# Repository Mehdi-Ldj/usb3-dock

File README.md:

# USB-C Dock with Gigabit Ethernet — Rev A

A 130 × 85 mm, four-layer dock built around a 7-port USB 3.2 Gen 1 hub:
Gigabit Ethernet, three USB-A ports, a USB-C downstream port and a USB 2.0
port, with every external port measured and protected.

## Design viewer

| Schematic | Board |
|:---:|:---:|
| [Schematic, seven pages (PDF)](docs/renders/schematic-rev-a.pdf) | [Open the PCB in KiCanvas][kicanvas] |

The PCB opens in the browser viewer; the schematic is hierarchical — a root
sheet and six children — which KiCanvas does not traverse, so it is published
as one PDF instead.

[kicanvas]: https://kicanvas.org/?repo=https%3A%2F%2Fgithub.com%2FMehdi-Ldj%2Fusb3-dock%2Fblob%2Fmain%2Fhardware%2Frev-a%2Fusb3-dock.kicad_pcb

## Overview

Power and data arrive on **two separate USB-C ports**. `J1` is a USB-C PD input
that negotiates 12 V and feeds the converters; `J2` is the upstream port that
presents the dock to the host as USB 3.2 Gen 1 — SuperSpeed plus USB 2.0.

Three choices shaped the board more than anything else:

- **The channel is budgeted, not assumed.** Every SuperSpeed pair runs in a
  90 Ω class on the outer layers over a solid inner ground, and the whole path
  from hub pin to connector was cascaded against a 6.5 dB budget before layout.
- **Every port is measured.** Five INA219 sit on 0.1 Ω shunts, one per external
  port, sharing one bus with no mux, so a fault is a number rather than a guess.
- **Power is poured, not routed.** Both inner layers are ground so that *both*
  outer layers can carry controlled-impedance pairs; the 5 V rail is a pour on
  the bottom layer instead of a trunk of tracks.

## Features

- **7-port USB 3.2 Gen 1** hub (USB5807C), 5 Gbps per port
- **Gigabit Ethernet** via LAN7800 with an integrated PHY and an RJ45 magjack
- **USB-C PD input** (CH224A) negotiating 12 V
- 12 V → **5 V @ 6 A**, 3.3 V and 1.2 V local rails
- **Per-port measurement** — five INA219 on 0.1 Ω shunts, one bus, no mux
- **Per-port protection** — under 100 ms trip, latched, retried at 2 s / 10 s / 60 s
- SuperSpeed muxing to the USB-C port (HD3SS3212, 2:1)
- **130 × 85 mm, 4-layer**, controlled impedance on 26 differential pairs
- Thermal and ESD design for a self-powered dock: 5 V pour on B.Cu, TVS on the input

## Board specifications

| Item | Value |
|---|---|
| Board size | **130 × 85 mm**, 4 layers |
| Stackup | **JLC04161H-3313**, FR4, 1.6 mm nominal |
| Copper | 1 oz outer, 0.5 oz inner, ENIG finish, green mask, white silk |
| Reference planes | **L2 and L3, both solid ground**, unbroken under every pair |
| Minimum feature | 0.15 mm track, 0.11 mm clearance, 0.20 mm drill |
| Vias | 0.20/0.50 mm and 0.30/0.60 mm, tented, no blind or buried |
| Impedance | 90 Ω SS/HS, 100 Ω MDI, 50 Ω single-ended, all ±10 % |
| Assembly | JLCPCB Standard PCBA |

## Architecture

Line colour and weight separate the five signal classes: power, SuperSpeed,
USB 2.0, Ethernet MDI and control. The PD sink on `J1` produces the 12 V rail,
which is fused and clamped before the 5 V converter; the hub fans out to the
three USB-A ports, the USB-C port through the mux, the Ethernet bridge and the
USB 2.0 port. Port power and sensing sit below the hub, between the 5 V rail and
the five VBUS outputs: the switches gate each port, the shunts measure it, and
the console sets enables and reads the measurements over the control lines.

## Design notes

### SuperSpeed channel

Every SuperSpeed and USB 2.0 pair runs at 0.180/0.150 mm in its 90 Ω class on
L1 or L4, over a solid inner ground. The outer dielectric is 3313 prepreg,
which keeps a 90 Ω pair to 0.51 mm of width and lets the fan-outs fit under the
0.4 mm hub.

The channel is closed by analysis rather than by hope: trace, AC coupling,
vias, launches and the mux S-parameters cascade to **−2.58 dB at 2.5 GHz**
against a **6.5 dB** budget, with the mux contributing 0.85 dB of it. The
100 nF AC-coupling capacitors sit on the transmit side at the connector, where
the ESD diodes already are.

Because a 1.5 mm tuning meander cannot fit inside a 2.0 mm uncoupled window,
the allowance for uncoupled length is 3.0 mm, and the two runs that exceed it
are recorded rather than hidden.

### Power and thermals

The 12 V input is fused at 3 A and clamped by an SMBJ15A before the
TPS56C215 buck, which holds 5 V at 6 A. That converter was chosen on junction
temperature, not on current: 5 V at 6 A in a 3.5 × 3.5 mm QFN sits at roughly
94 °C junction at 40 °C ambient, and the 2 × 3 mm class was rejected on its
measured thermal resistance.

The 5 V rail is a pour on B.Cu rather than a trunk of tracks. That took the
drop at a fully loaded port from 231 mV to 27 mV and cut the copper loss from
about 750 mW to under 100 mW.

### Ethernet

The LAN7800 carries the MDI on a 100 Ω class to a magjack with integrated
magnetics and a Bob Smith termination, so no discrete transformer or common-mode
choke is needed. The MDI pairs are length-matched and stay on L1 for the whole
run.

### Port sensing and protection

Each external port has a TPS2065 switch and a 0.1 Ω shunt with an INA219 across
it, so current, voltage and power are measured rather than inferred. The hub's
port-power and overcurrent sense share one pin per port; the controller joins
that node with an open-drain pin, making it a wired-OR — either side can force a
port off, neither can force one on.

### Package and assembly

Four layers carry the 0.4 mm hub fan-out on the top, both inner layers as solid
ground, and the signal pairs on the bottom. The QFNs and the magjack have pads
underneath, so assembly is a stencil-and-reflow job rather than hand work; the
placement file carries the rotation corrections the assembler's part library
needs, measured once against their preview.

## Layout

| Front copper | Back copper |
|:---:|:---:|
|  |  |
| **Inner 1 — ground plane** | **Inner 2 — ground plane** |
|  |  |

Both inner layers are unbroken ground; the 5 V pour is the large region on the
back copper. The top view of the assembled board is
[`board-3d-top.png`](docs/renders/board-3d-top.png).

## Repository structure

| Path | Contents |
|---|---|
| `hardware/rev-a/` | KiCad 10 project: six schematic sheets, PCB, symbol and footprint libraries, 3D models, JLCPCB BOM |
| `docs/` | [BOM](docs/BOM.md), block diagram, board renders, schematic PDF |
| `LICENSE` | CERN Open Hardware Licence v2 — Permissive |

Open the project with KiCad 10:

```bash
kicad hardware/rev-a/usb3-dock.kicad_pro
```

## Fabrication and assembly

The board is drawn for JLCPCB 4-layer fabrication on the **JLC04161H-3313**
stackup with impedance control enabled at ±10 %, and for Standard PCBA with the
stencil and reflow that the QFN packages require.

The fabrication package for a release — gerbers, drill file, job file, BOM and
CPL — is attached to the release rather than committed here.

## Status

**Rev A is frozen and has not been fabricated yet.** The design is complete
through DRC, ERC and schematic/board parity.

## Licence

Released under the [CERN Open Hardware Licence Version 2 – Permissive](LICENSE).

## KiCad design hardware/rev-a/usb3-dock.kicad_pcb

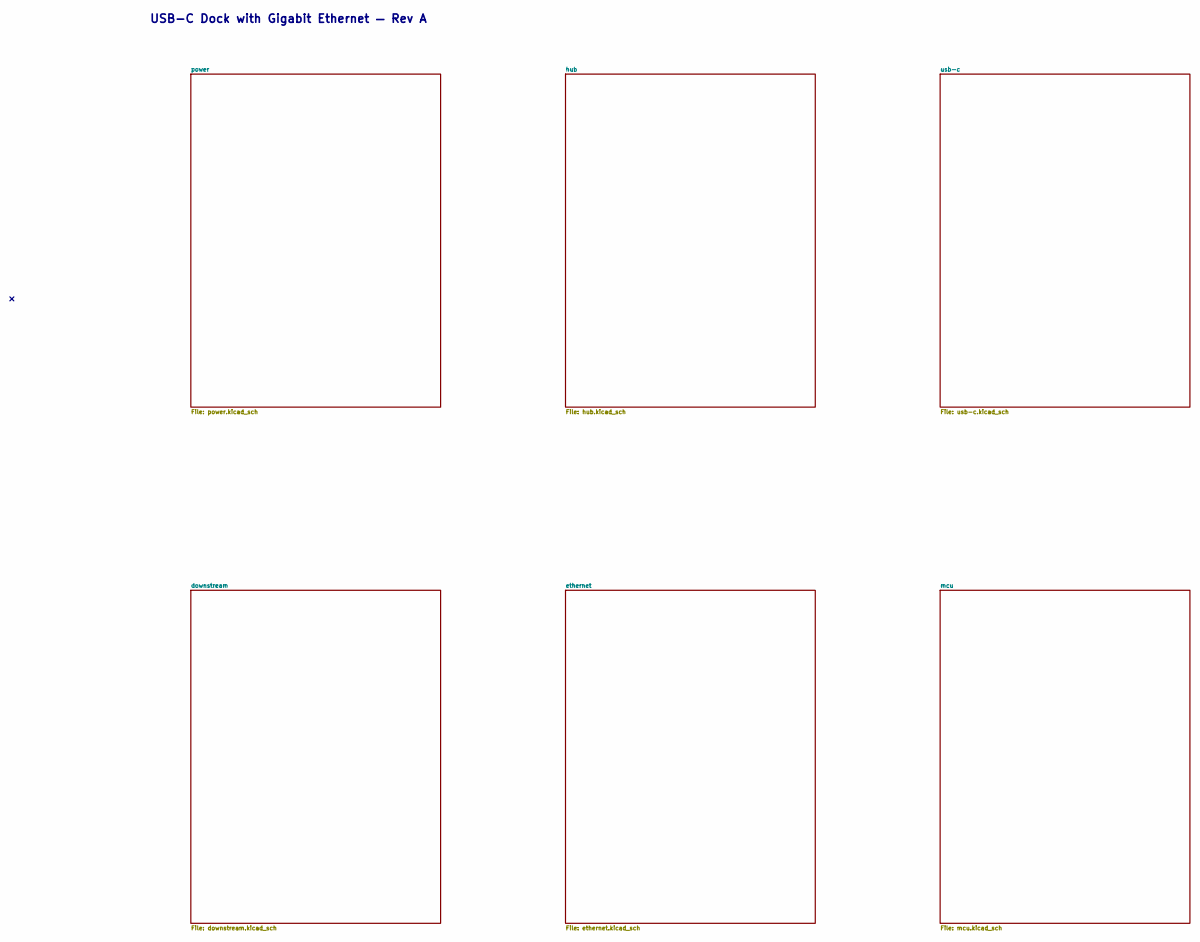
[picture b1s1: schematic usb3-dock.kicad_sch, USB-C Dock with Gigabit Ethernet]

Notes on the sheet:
USB-C Dock with Gigabit Ethernet — Rev A

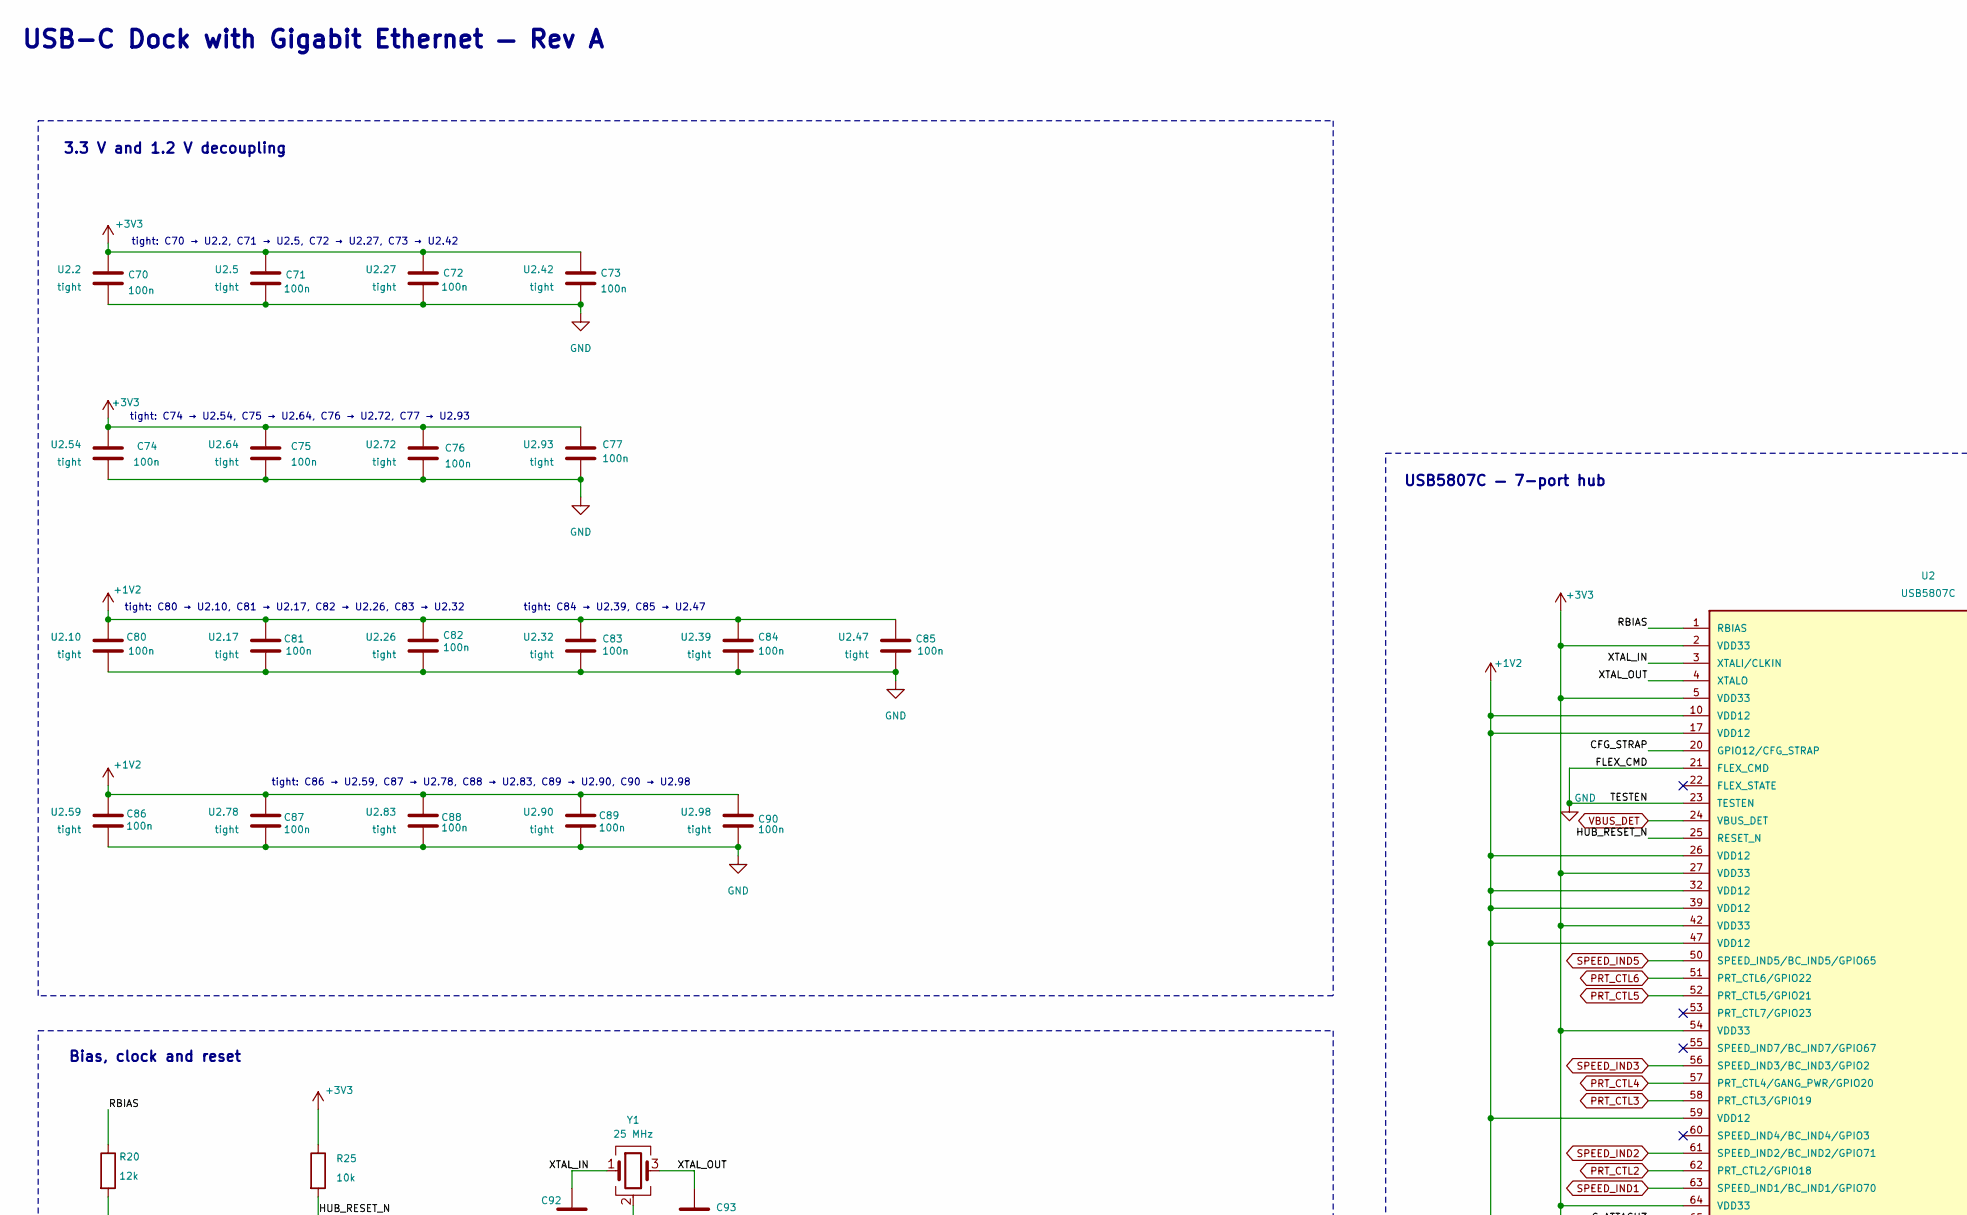
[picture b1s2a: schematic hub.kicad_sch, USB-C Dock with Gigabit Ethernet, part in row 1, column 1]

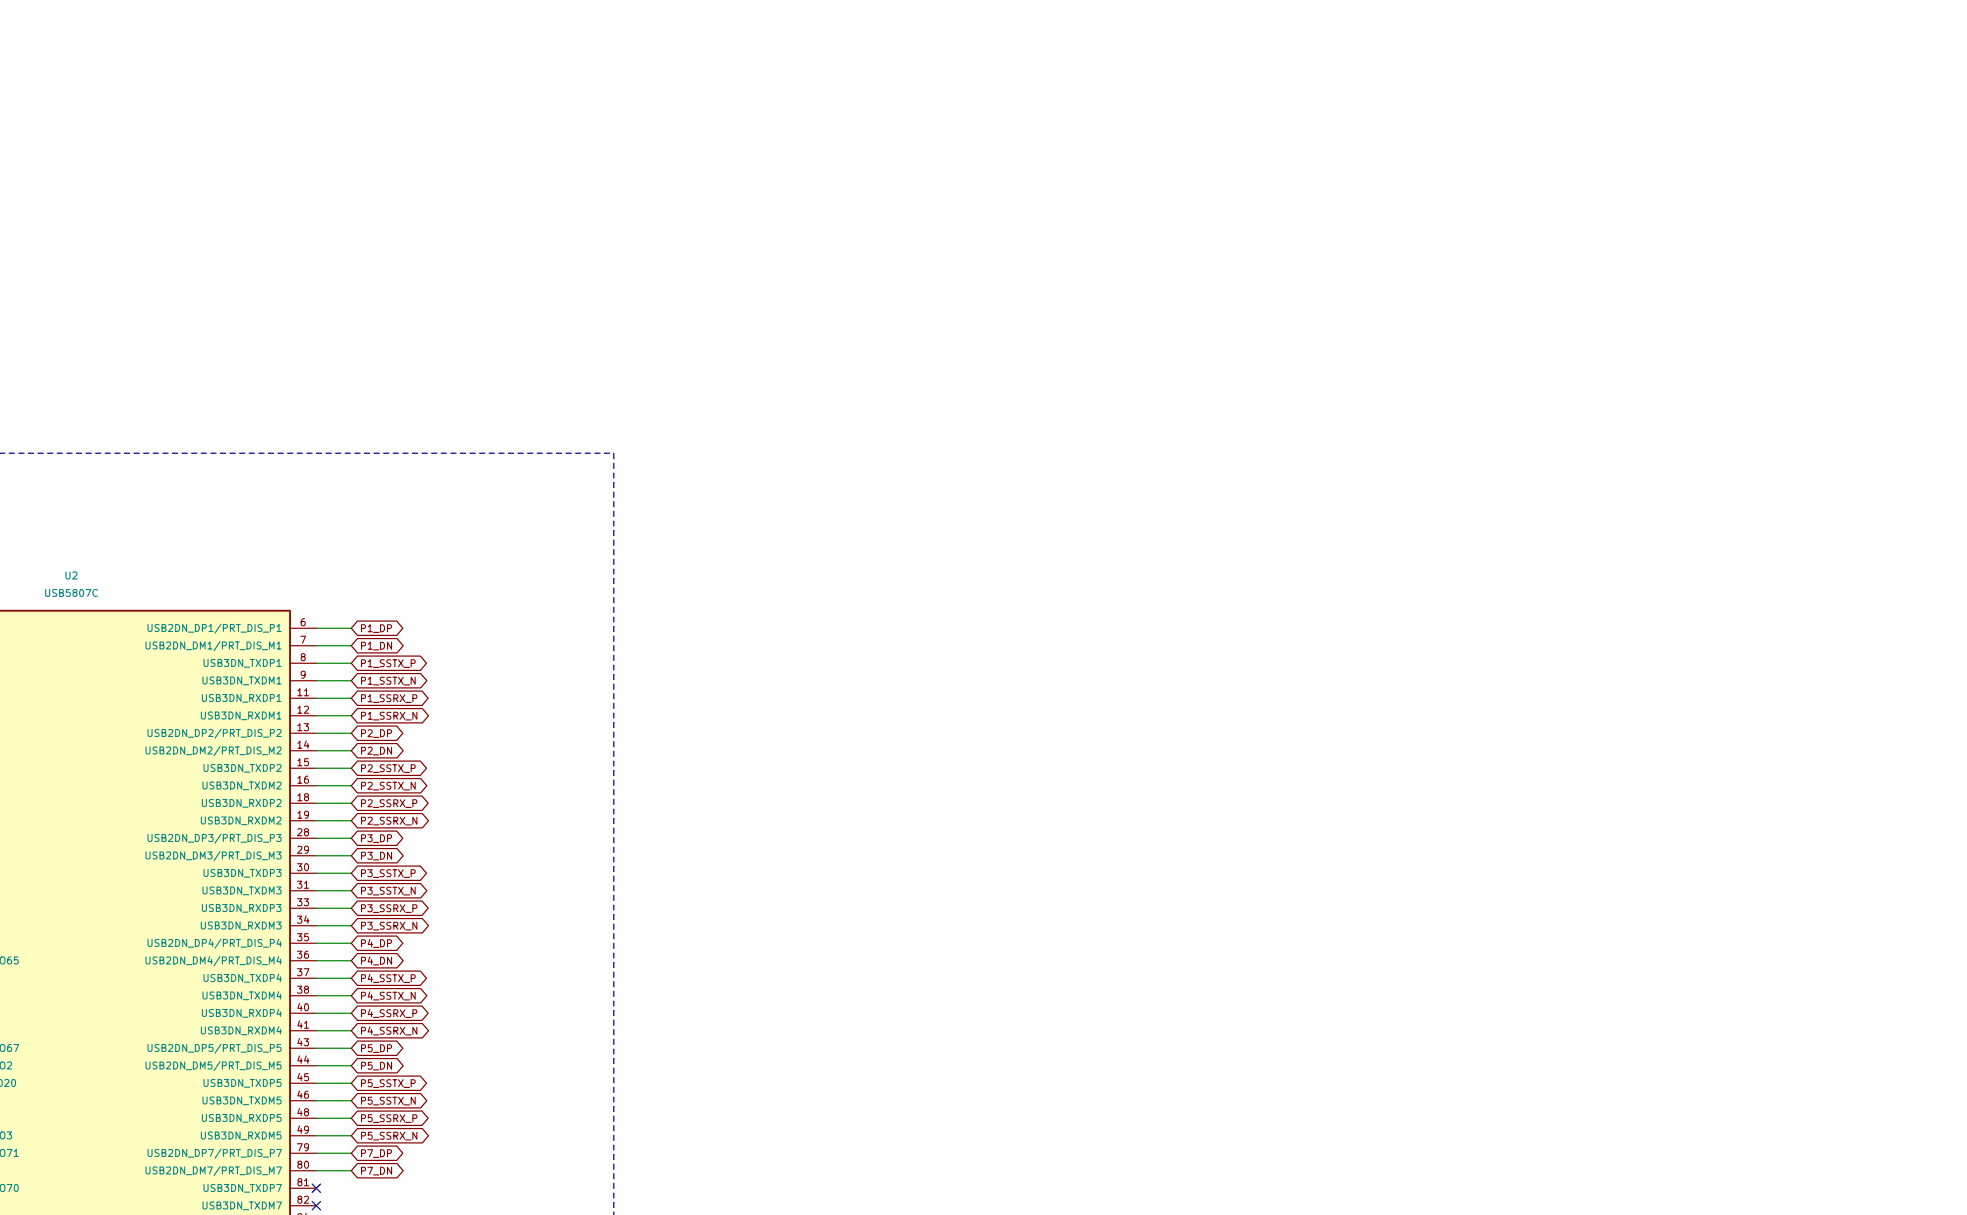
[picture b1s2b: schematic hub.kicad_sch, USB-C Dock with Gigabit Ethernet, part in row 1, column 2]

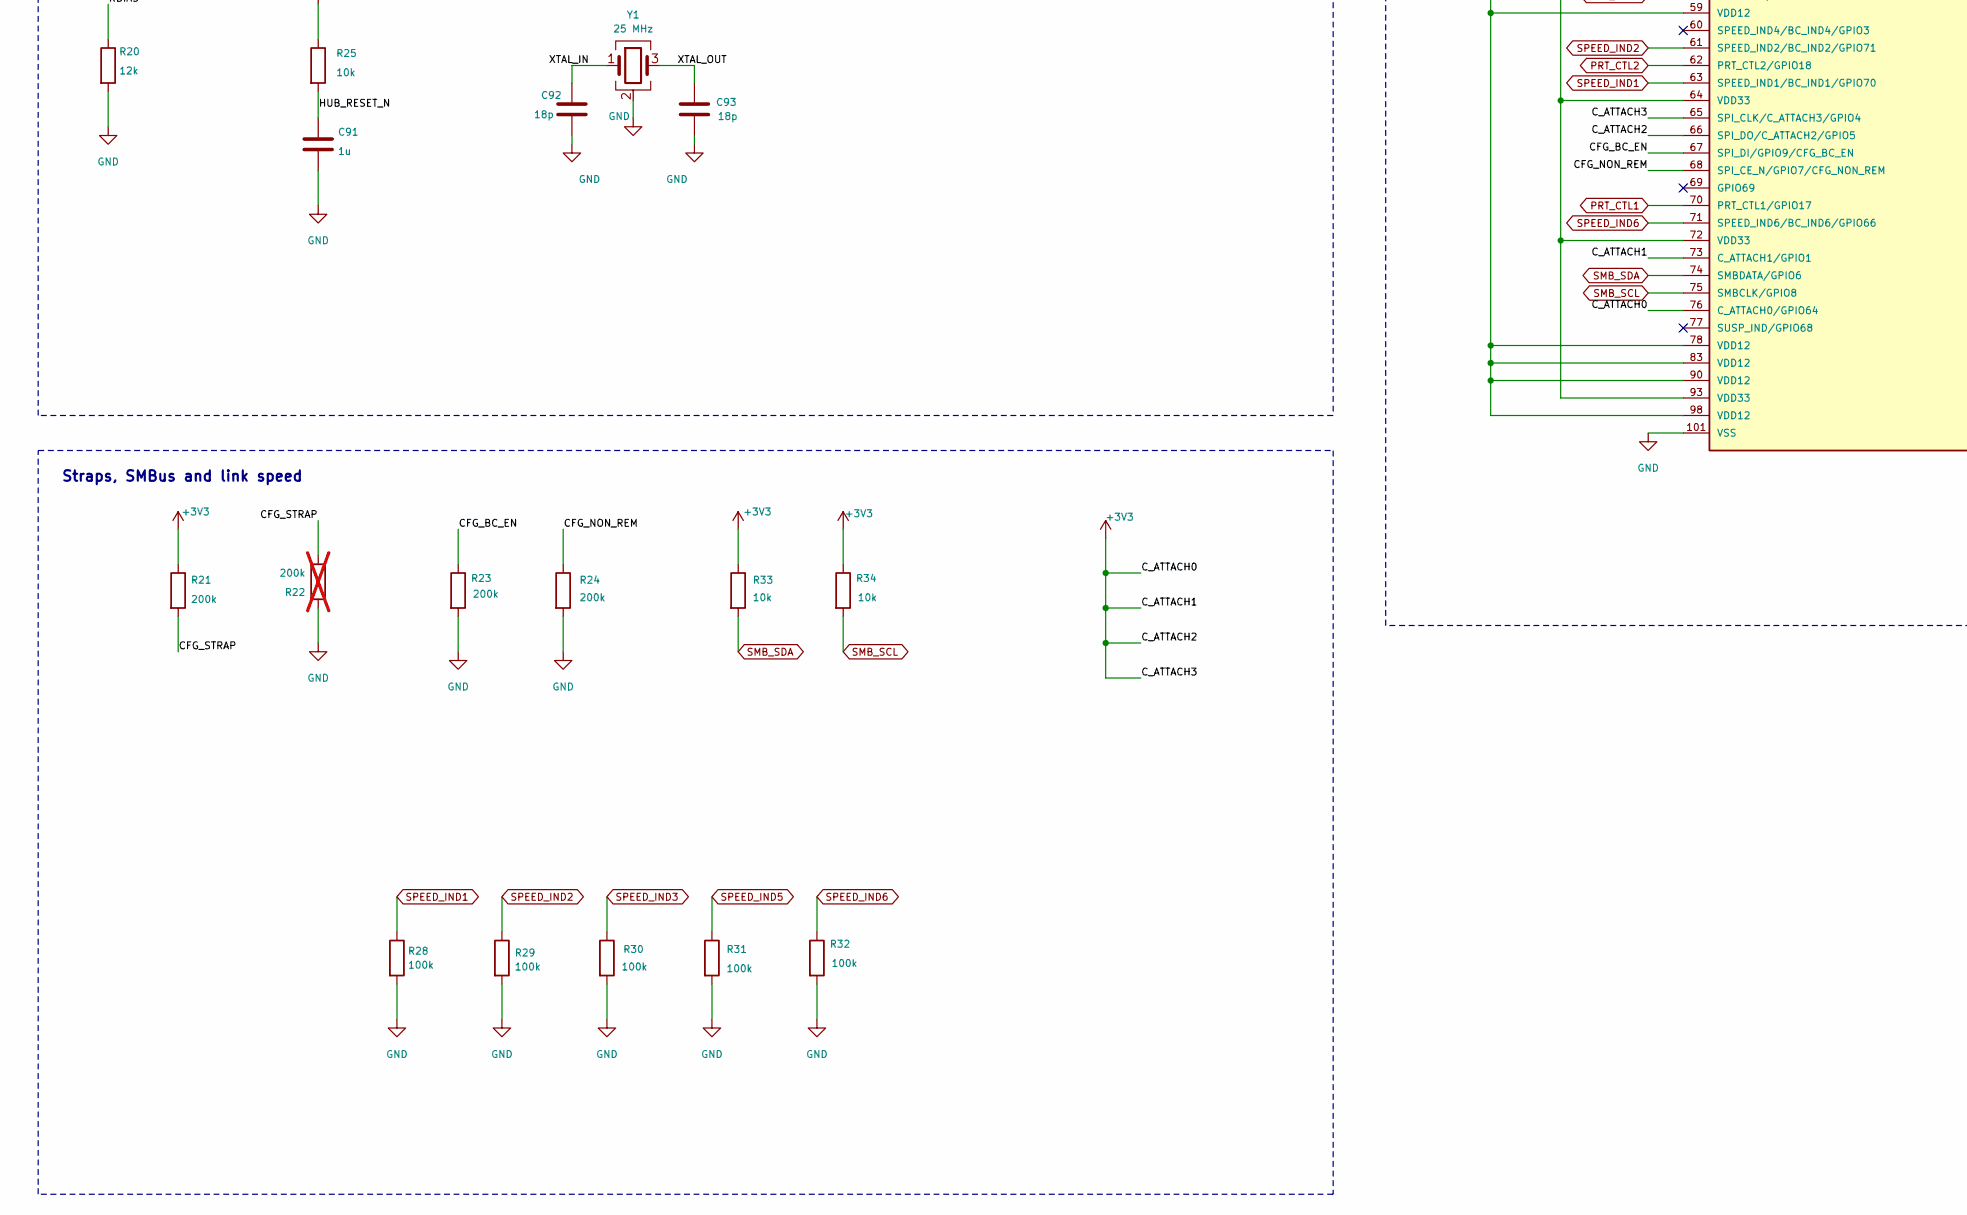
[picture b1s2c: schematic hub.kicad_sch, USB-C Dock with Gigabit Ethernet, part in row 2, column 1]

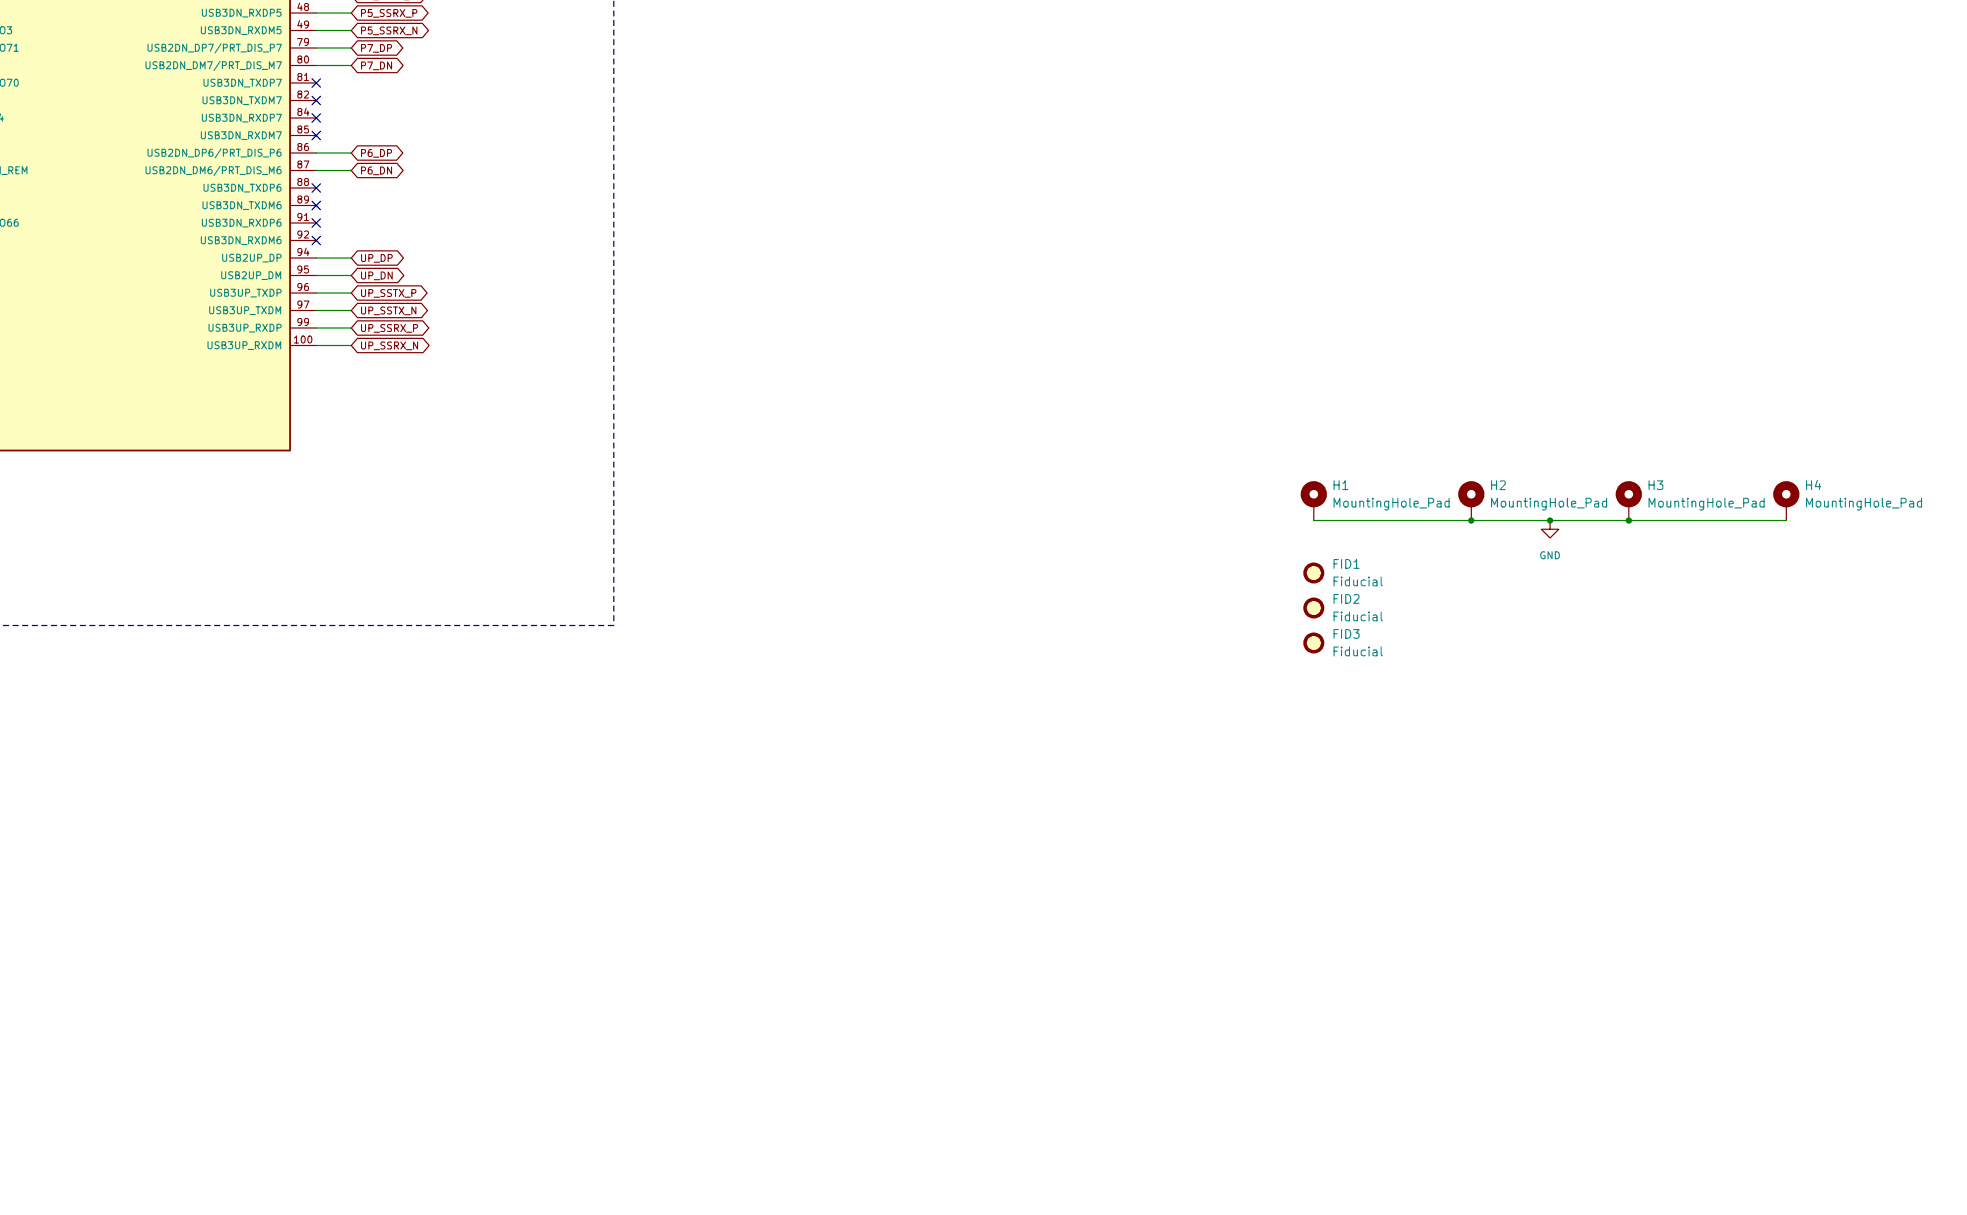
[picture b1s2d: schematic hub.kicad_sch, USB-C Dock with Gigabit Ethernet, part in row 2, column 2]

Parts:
C70, C71, C72, C73, C74, C75, C76, C77, C80, C81, C82, C83, C84, C85, C86, C87, C88, C89, C90: 100n; C_0402_1005Metric
C91: 1u; C_0603_1608Metric
C92, C93: 18p; C_0402_1005Metric
FID1, FID2, FID3: Fiducial; Fiducial_1mm_Mask2mm
H1, H2, H3, H4: MountingHole_Pad; MountingHole_3.5mm_Pad_Via
R20: 12k; R_0603_1608Metric
R21, R23, R24: 200k; R_0603_1608Metric
R22: 200k; R_0603_1608Metric; not fitted
R25, R33, R34: 10k; R_0603_1608Metric
R28, R29, R30, R31, R32: 100k; R_0603_1608Metric
U2: USB5807C; VQFN-100-1EP_12x12mm_P0.4mm_EP8x8mm
Y1: 25 MHz; Crystal_SMD_3225-4Pin_3.2x2.5mm

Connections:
+1V2: C80.1, C81.1, C82.1, C83.1, C84.1, C85.1, C86.1, C87.1, C88.1, C89.1, C90.1, U2.10 (VDD12), U2.17 (VDD12), U2.26 (VDD12), U2.32 (VDD12), U2.39 (VDD12), U2.47 (VDD12), U2.59 (VDD12), U2.78 (VDD12), U2.83 (VDD12), U2.90 (VDD12), U2.98 (VDD12); also elsewhere on the board
+3V3: C70.1, C71.1, C72.1, C73.1, C74.1, C75.1, C76.1, C77.1, R21.1, R25.1, R33.1, R34.1, U2.2 (VDD33), U2.5 (VDD33), U2.27 (VDD33), U2.42 (VDD33), U2.54 (VDD33), U2.64 (VDD33), U2.65 (SPI_CLK/C_ATTACH3/GPIO4), U2.66 (SPI_DO/C_ATTACH2/GPIO5), U2.72 (VDD33), U2.73 (C_ATTACH1/GPIO1), U2.76 (C_ATTACH0/GPIO64), U2.93 (VDD33); also elsewhere on the board
/hub/CFG_BC_EN: R23.1, U2.67 (SPI_DI/GPIO9/CFG_BC_EN)
/hub/CFG_NON_REM: R24.1, U2.68 (SPI_CE_N/GPIO7/CFG_NON_REM)
/hub/CFG_STRAP: R21.2, R22.2, U2.20 (GPIO12/CFG_STRAP)
/hub/HUB_RESET_N: C91.1, R25.2, U2.25 (RESET_N)
/hub/RBIAS: R20.1, U2.1 (RBIAS)
/hub/XTAL_IN: C92.1, U2.3 (XTALI/CLKIN), Y1.1
/hub/XTAL_OUT: C93.1, U2.4 (XTALO), Y1.3
GND: C70.2, C71.2, C72.2, C73.2, C74.2, C75.2, C76.2, C77.2, C80.2, C81.2, C82.2, C83.2, C84.2, C85.2, C86.2, C87.2, C88.2, C89.2, C90.2, C91.2, C92.2, C93.2, H1.1 (1_1), H2.1 (1_1), H3.1 (1_1), H4.1 (1_1), R20.2, R22.1, R23.2, R24.2, R28.2, R29.2, R30.2, R31.2, R32.2, U2.21 (FLEX_CMD), U2.23 (TESTEN), U2.101 (VSS), Y1.2 (G), Y1.4 (G); also elsewhere on the board
P1_DN: U2.7 (USB2DN_DM1/PRT_DIS_M1); also elsewhere on the board
P1_DP: U2.6 (USB2DN_DP1/PRT_DIS_P1); also elsewhere on the board
P1_SSRX_N: U2.12 (USB3DN_RXDM1); also elsewhere on the board
P1_SSRX_P: U2.11 (USB3DN_RXDP1); also elsewhere on the board
P1_SSTX_N: U2.9 (USB3DN_TXDM1); also elsewhere on the board
P1_SSTX_P: U2.8 (USB3DN_TXDP1); also elsewhere on the board
P2_DN: U2.14 (USB2DN_DM2/PRT_DIS_M2); also elsewhere on the board
P2_DP: U2.13 (USB2DN_DP2/PRT_DIS_P2); also elsewhere on the board
P2_SSRX_N: U2.19 (USB3DN_RXDM2); also elsewhere on the board
P2_SSRX_P: U2.18 (USB3DN_RXDP2); also elsewhere on the board
P2_SSTX_N: U2.16 (USB3DN_TXDM2); also elsewhere on the board
P2_SSTX_P: U2.15 (USB3DN_TXDP2); also elsewhere on the board
P3_DN: U2.29 (USB2DN_DM3/PRT_DIS_M3); also elsewhere on the board
P3_DP: U2.28 (USB2DN_DP3/PRT_DIS_P3); also elsewhere on the board
P3_SSRX_N: U2.34 (USB3DN_RXDM3); also elsewhere on the board
P3_SSRX_P: U2.33 (USB3DN_RXDP3); also elsewhere on the board
P3_SSTX_N: U2.31 (USB3DN_TXDM3); also elsewhere on the board
P3_SSTX_P: U2.30 (USB3DN_TXDP3); also elsewhere on the board
P4_DN: U2.36 (USB2DN_DM4/PRT_DIS_M4); also elsewhere on the board
P4_DP: U2.35 (USB2DN_DP4/PRT_DIS_P4); also elsewhere on the board
P4_SSRX_N: U2.41 (USB3DN_RXDM4); also elsewhere on the board
P4_SSRX_P: U2.40 (USB3DN_RXDP4); also elsewhere on the board
P4_SSTX_N: U2.38 (USB3DN_TXDM4); also elsewhere on the board
P4_SSTX_P: U2.37 (USB3DN_TXDP4); also elsewhere on the board
P5_DN: U2.44 (USB2DN_DM5/PRT_DIS_M5); also elsewhere on the board
P5_DP: U2.43 (USB2DN_DP5/PRT_DIS_P5); also elsewhere on the board
P5_SSRX_N: U2.49 (USB3DN_RXDM5); also elsewhere on the board
P5_SSRX_P: U2.48 (USB3DN_RXDP5); also elsewhere on the board
P5_SSTX_N: U2.46 (USB3DN_TXDM5); also elsewhere on the board
P5_SSTX_P: U2.45 (USB3DN_TXDP5); also elsewhere on the board
P6_DN: U2.87 (USB2DN_DM6/PRT_DIS_M6); also elsewhere on the board
P6_DP: U2.86 (USB2DN_DP6/PRT_DIS_P6); also elsewhere on the board
P7_DN: U2.80 (USB2DN_DM7/PRT_DIS_M7); also elsewhere on the board
P7_DP: U2.79 (USB2DN_DP7/PRT_DIS_P7); also elsewhere on the board
PRT_CTL1: U2.70 (PRT_CTL1/GPIO17); also elsewhere on the board
PRT_CTL2: U2.62 (PRT_CTL2/GPIO18); also elsewhere on the board
PRT_CTL3: U2.58 (PRT_CTL3/GPIO19); also elsewhere on the board
PRT_CTL4: U2.57 (PRT_CTL4/GANG_PWR/GPIO20); also elsewhere on the board
PRT_CTL5: U2.52 (PRT_CTL5/GPIO21); also elsewhere on the board
PRT_CTL6: U2.51 (PRT_CTL6/GPIO22); also elsewhere on the board
SMB_SCL: R34.2, U2.75 (SMBCLK/GPIO8); also elsewhere on the board
SMB_SDA: R33.2, U2.74 (SMBDATA/GPIO6); also elsewhere on the board
SPEED_IND1: R28.1, U2.63 (SPEED_IND1/BC_IND1/GPIO70); also elsewhere on the board
SPEED_IND2: R29.1, U2.61 (SPEED_IND2/BC_IND2/GPIO71); also elsewhere on the board
SPEED_IND3: R30.1, U2.56 (SPEED_IND3/BC_IND3/GPIO2); also elsewhere on the board
SPEED_IND5: R31.1, U2.50 (SPEED_IND5/BC_IND5/GPIO65); also elsewhere on the board
SPEED_IND6: R32.1, U2.71 (SPEED_IND6/BC_IND6/GPIO66); also elsewhere on the board
UP_DN: U2.95 (USB2UP_DM); also elsewhere on the board
UP_DP: U2.94 (USB2UP_DP); also elsewhere on the board
UP_SSRX_N: U2.100 (USB3UP_RXDM); also elsewhere on the board
UP_SSRX_P: U2.99 (USB3UP_RXDP); also elsewhere on the board
UP_SSTX_N: U2.97 (USB3UP_TXDM); also elsewhere on the board
UP_SSTX_P: U2.96 (USB3UP_TXDP); also elsewhere on the board
VBUS_DET: U2.24 (VBUS_DET); also elsewhere on the board

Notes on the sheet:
tight: C80 → U2.10, C81 → U2.17, C82 → U2.26, C83 → U2.32
Straps, SMBus and link speed
USB-C Dock with Gigabit Ethernet — Rev A
Bias, clock and reset
tight: C70 → U2.2, C71 → U2.5, C72 → U2.27, C73 → U2.42
tight: C84 → U2.39, C85 → U2.47
tight: C86 → U2.59, C87 → U2.78, C88 → U2.83, C89 → U2.90, C90 → U2.98
USB5807C — 7-port hub
3.3 V and 1.2 V decoupling
tight: C74 → U2.54, C75 → U2.64, C76 → U2.72, C77 → U2.93
